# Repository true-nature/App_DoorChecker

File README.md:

App_DoorChecker
===============

The wireless monitor of the door lock up status.
It works on ToCoS TWE-Lite.

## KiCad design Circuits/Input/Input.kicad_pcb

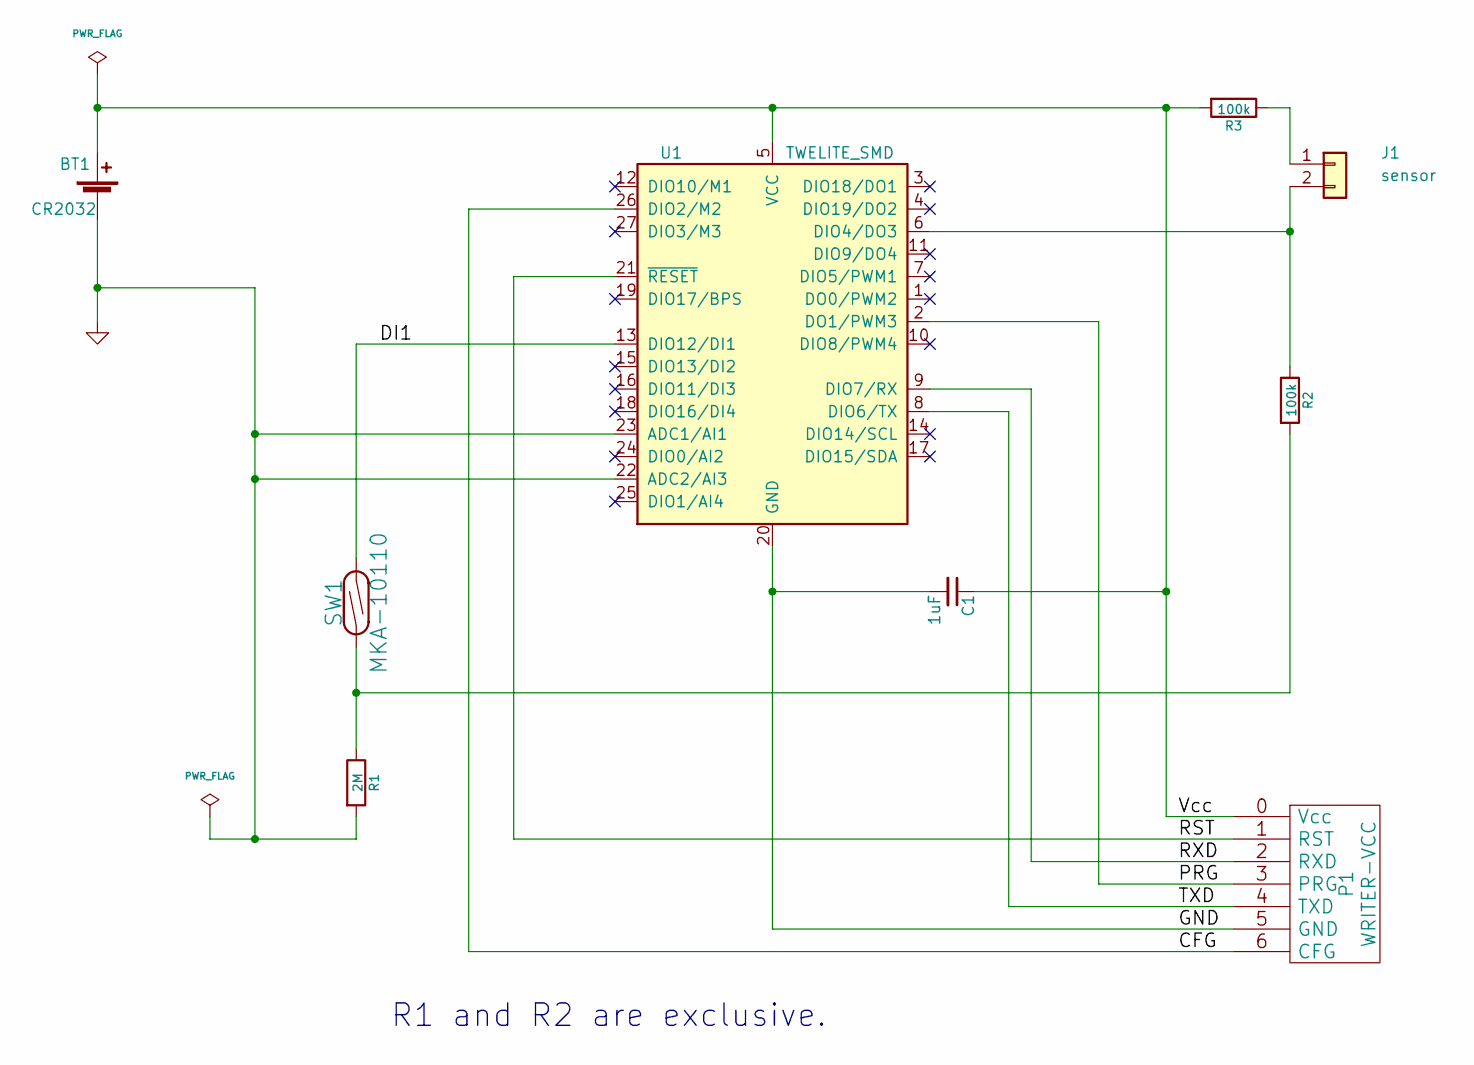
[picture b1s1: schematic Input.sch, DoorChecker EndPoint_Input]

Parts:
BT1: CR2032; PBCS-75
C1: 1uF; C_0603_1608Metric_Pad0.84x1.00mm_HandSolder
J1: sensor; PinHeader_2x01_P2.54mm_Vertical
P1: WRITER-VCC; WRITE-7P
R1: 2M; R_0603_1608Metric_Pad0.84x1.00mm_HandSolder
R2, R3: 100k; R_0603_1608Metric_Pad0.84x1.00mm_HandSolder
SW1: MKA-10110
U1: TWELITE_SMD

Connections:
/CFG: P1.6 (CFG), U1.26 (DIO2/M2)
/DI1: SW1.2, U1.13 (DIO12/DI1)
/PRG: P1.3 (PRG), U1.2 (DO1/PWM3)
/RST: P1.1 (RST), U1.21 (~RESET)
/RXD: P1.2 (RXD), U1.9 (DIO7/RX)
/TXD: P1.4 (TXD), U1.8 (DIO6/TX)
/Vcc: BT1.1 (+), C1.1, P1.0 (Vcc), R3.2, U1.5 (VCC)
GND: BT1.2 (-), C1.2, P1.5 (GND), R1.2, U1.20 (GND), U1.22 (ADC2/AI3), U1.23 (ADC1/AI1), U1.28 (GND), U1.30 (GND), U1.31 (GND), U1.32 (GND)
unnamed: J1.1, R3.1
unnamed: J1.2, R2.1, U1.6 (DIO4/DO3)
unnamed: R1.1, R2.2, SW1.1

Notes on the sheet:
R1 and R2 are exclusive.

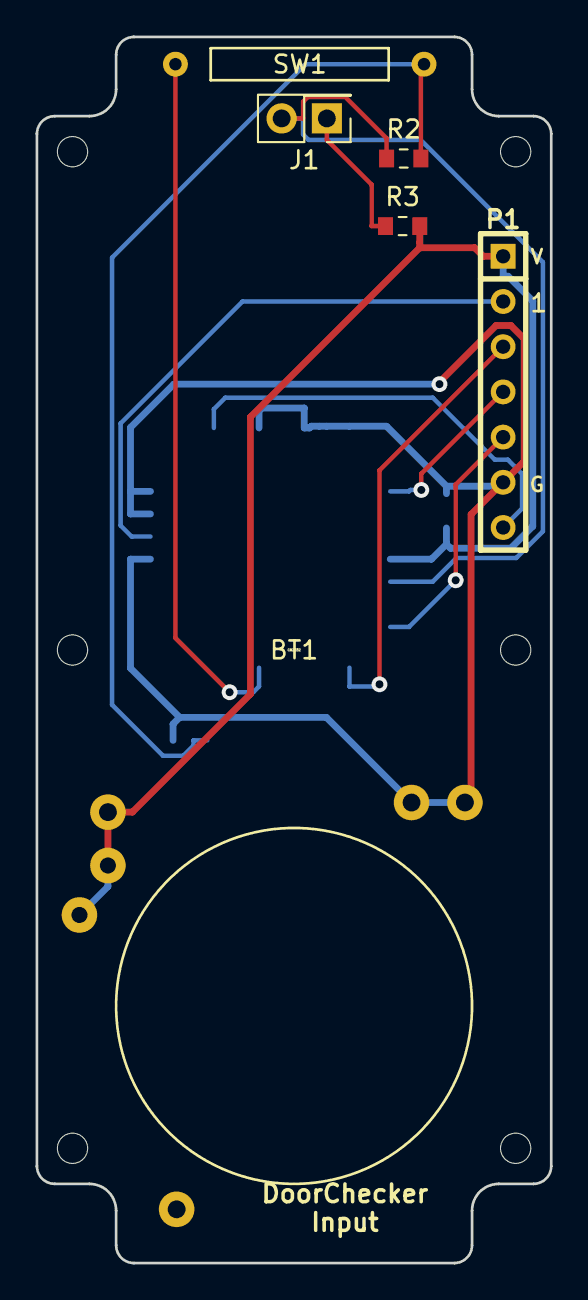
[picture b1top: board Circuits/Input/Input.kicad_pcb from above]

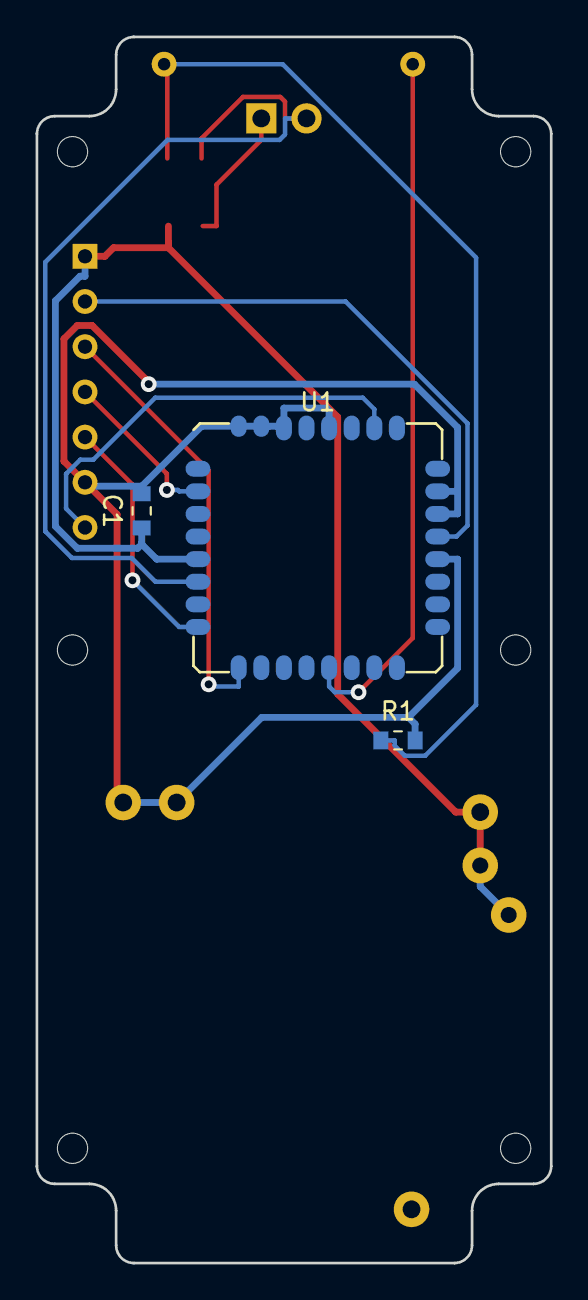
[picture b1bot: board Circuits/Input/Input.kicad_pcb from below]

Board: 2 copper layers, 28.9 x 68.9 mm, 9 parts (3 on the bottom side), 11 nets.

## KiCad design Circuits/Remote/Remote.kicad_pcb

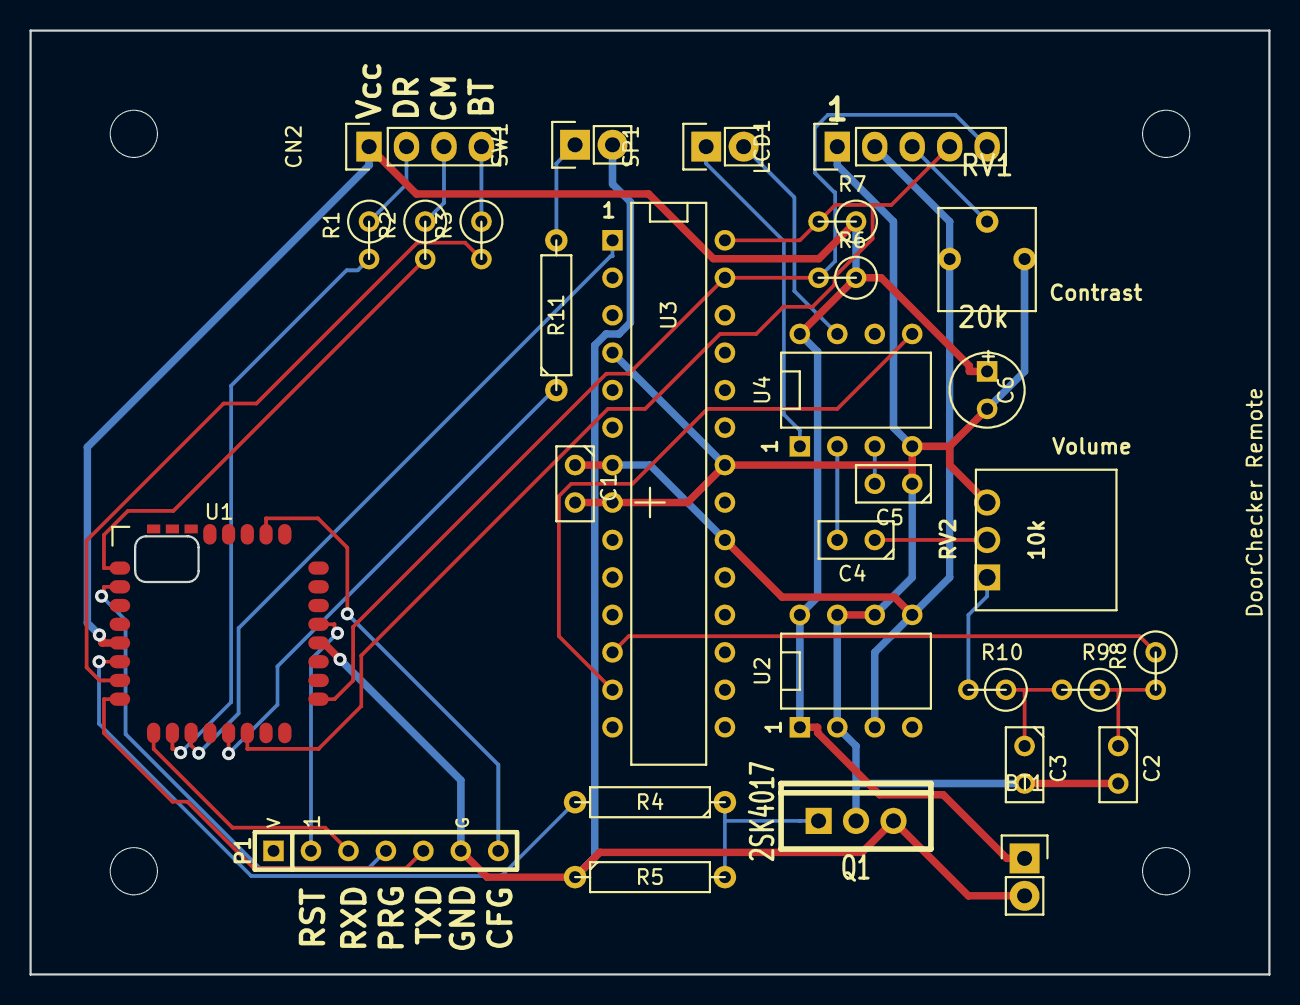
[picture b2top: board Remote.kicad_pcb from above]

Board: 2 copper layers, 84.0 x 64.0 mm, 31 parts (0 on the bottom side), 33 nets.

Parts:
BT1: BATTERY; Pin_Header_Straight_1x02
C1: 0.1u; C1
C2: 0.047u; C1
C3: 0.01u; C1
C4, C5: 1u; C1
C6: 47u; C1V5
CN2: CONN_4; Pin_Header_Straight_1x04
DoorChecker Remote: VAL**; PB-SGM-135
LCD1: AQM1602NI; Pin_Header_Straight_1x05
P1: WRITER-VCC; WRITE-7P
Q1: 2SK4017; TO220_VERT_GDS
R1, R2, R3: 680; R1
R4: 1k; R4
R5: 2.2M; R4
R6, R7, R10: 10k; R1
R8: 1k; R1
R9: 4.7k; R1
R11: 10k; R4
RV1: 20k; RV-3362P
RV2: 10k; RV-TSR-3386T
SP1: SPEAKER; Pin_Header_Straight_1x02
SW1: WakeUp; Pin_Header_Straight_1x02
U1: TWE_LITE_SMD; TWE-001L-SMD
U2: STEPUP3.3V; DIP-8__300
U3: ATP3011-PU; DIP-28__300
U4: HT82V739; DIP-8__300

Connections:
/3.3VOUT: C1.1, LCD1.2, RV1.1, U2.3, U2.5, U3.7, U3.20
/AOUT: R8.1, U3.12
/AudioIn: C4.2, U4.2
/BATT: CN2.4, R3.1
/COMM: CN2.3, R2.1
/DOOR: CN2.2, R1.1
/GND_SW: R4.2, U1.6
/Gate: Q1.G, R4.1, R5.2
/LPF1: C2.1, R8.2, R9.1
/LPF2: C3.1, R9.2, R10.1
/LPF3: R10.2, RV2.1
/M2: P1.6, U1.26
/PLAY#: U3.13, U4.5
/PRG: P1.3, U1.2
/PWM1: R3.2, U1.7
/PWM2: R2.2, U1.1
/PWM4: R1.2, U1.10
/QGND: C1.2, C2.2, C3.2, C5.1, C6.2, LCD1.1, Q1.D, RV1.3, RV2.3, U2.2, U2.6, U2.7, U3.4, U3.8, U3.22, U4.4
/RESET#: U1.11, U3.1
/RST: P1.1, U1.21
/RXD: P1.2, U1.9
/SCL: LCD1.4, R7.2, U1.14, U3.28
/SDA: LCD1.5, R6.2, U1.17, U3.27
/SPK+: SP1.1, U4.1
/SPK-: SP1.2, U4.7
/SW: R11.2, SW1.1
/TXD: P1.4, U1.8
/V0: LCD1.3, RV1.2
/VOL: C4.1, RV2.2
/VREF: C5.2, U4.3
/WUP: R11.1, U1.13
GND: BT1.2, P1.5, Q1.S, R5.1, SW1.2, U1.20
VCC: BT1.1, C6.1, CN2.1, R6.1, R7.1, U1.5, U2.1, U2.8, U4.8

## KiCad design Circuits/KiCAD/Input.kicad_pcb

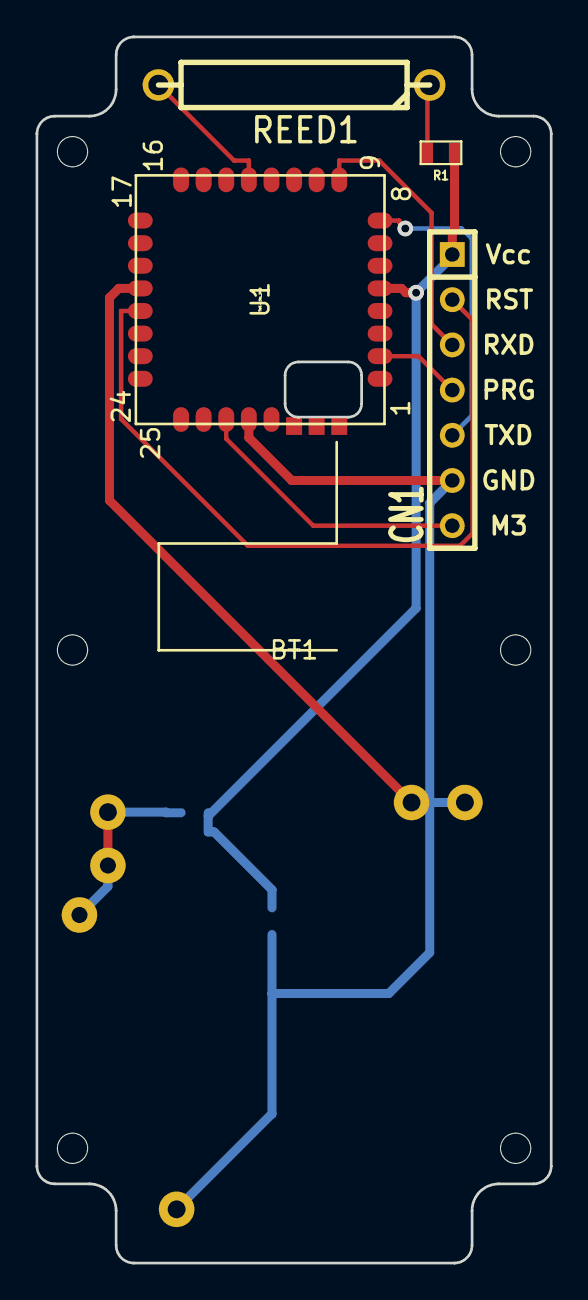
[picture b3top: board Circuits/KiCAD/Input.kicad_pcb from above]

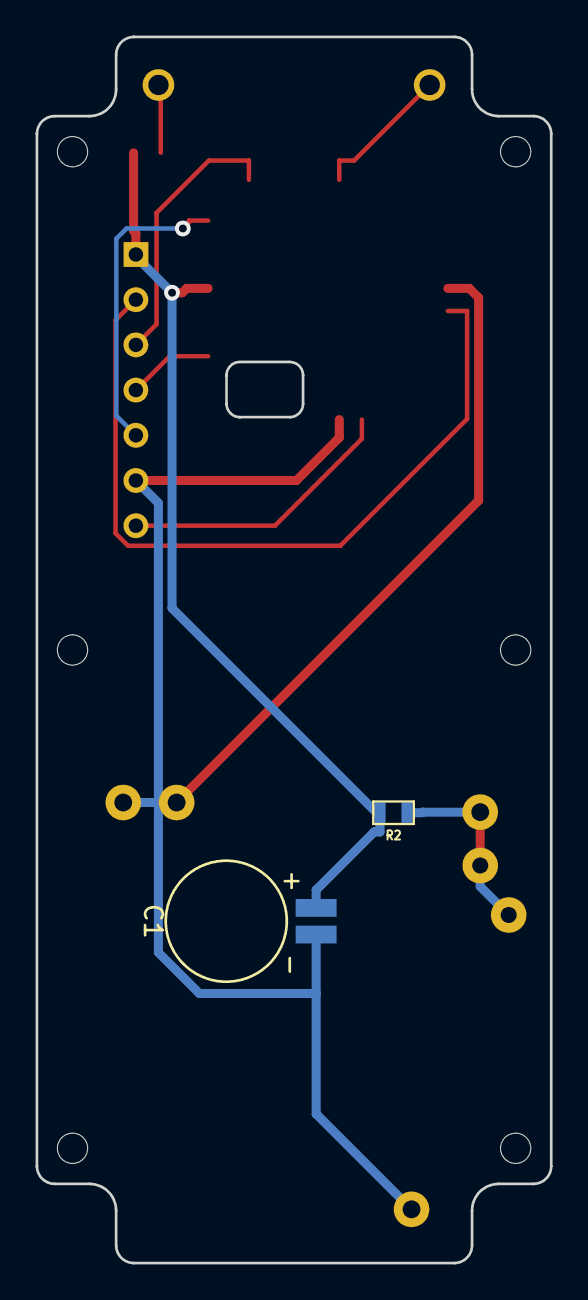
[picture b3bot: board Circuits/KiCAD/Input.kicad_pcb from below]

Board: 2 copper layers, 28.9 x 68.9 mm, 7 parts (2 on the bottom side), 10 nets.

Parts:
BT1: CR2032; PBCS-75
C1: 0.22; DCK-3R3E224-E
CN1: WRITER; SIL-7
R1: 2M; SM0603
R2: 75; SM0603
REED1: SPST; R6
U1: TWE-Lite_SMD; TWE-001L-SMD

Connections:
/CFG: CN1.7, U1.27
/DC3V: BT1.1, R2.1
/DOOR: REED1.2, U1.13
/PRG: CN1.4, U1.2
/PULLUP: R1.1, REED1.1
/RST: CN1.2, U1.21
/RX: CN1.3, U1.9
/TX: CN1.5, U1.8
GND: BT1.2, C1.2, CN1.6, U1.20, U1.28
VCC: C1.1, CN1.1, R1.2, R2.2, U1.5

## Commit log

2014-09-25 Ignore firmware binaries.
2014-09-25 Updated project description.
2014-09-25 Imported from Samp_Monitor v1.3.2 project.
2014-09-25 Updated to Samp_Monitor v1.3.3.
2014-09-25 Changed application name.
2014-09-25 Eclipseのコード解釈エラーを解決。
2014-09-25 プルアップ停止判定のタイミングを確認するToDoタスクを追加。
2014-09-25 Making up a ToDo list.
2014-09-26 ToDo項目をリストアップ中。
2014-09-26 readmeの中身を改造後の予定動作に差し替え。
2014-09-26 EEPROM読み込み前では設定値がプルアップ判定に反映されないので、読み込み後に移動。
2014-09-27 Eclipseのコード解釈エラーを解消。
2014-09-27 子機のドアアラームを無効化。定期的に状態送信を有効化。
2014-09-27 App_Twelite v1.7の実験的な実装からI2C接続LCDのコードをコピー。
2014-09-27 I2C LCD functions are ready to call.
2014-09-27 子機の数をEEPROMに記憶。
2014-09-27 実装が済んだToDoのマークアップを削除。
2014-09-28 子機使用状況を最大数でなく使用IDのマスクで管理する。
2014-09-28 ADCを有効にして電源電圧をモニターする。
2014-09-28 32bit all 1は特異値なので使用不可。ビット数を減らして子機は最大30とする。
2014-09-28 flash.cがconfig.hをincludeしないので無条件でフィールド追加。
2014-09-28 u32idmaskは0にできない。
2014-09-28 パケット受信時にスイッチ状態、子機ID,電源電圧を保存。
2014-09-28 配列の先頭から使用する。
2014-09-28 2行8桁のLCDで表示できる数に制限。
2014-09-28 I2C LCD(AQM0802A)でステータスを表示する。
2014-09-28 通信途絶の場合は低電圧と同じ表示。
2014-09-29 Designing the circuit.
2014-09-29 Revert "子機のドアアラームを無効化。定期的に状態送信を有効化。"
    This reverts commit 1dabc5c033cbefd2f427b25f9b8f2b4ddbc21269.
    Conflicts:
    Common/Source_User/config.h
    EndDevice_Input/Source/ProcessEv_Door_Timer.c
2014-09-29 子機モード51からFEへ軌道変更。
2014-09-29 PKT_ID_BOTTON用に変更中。
2014-09-29 tsRxPktInfoをアドレス私に変更。
2014-09-29 子機モード0x51(PKT_ID_BOTTON)を定時送信化して戸締りチェッカー再実装。
2014-09-29 Moved I2C_impl to Common. Endpoint_Remote will use it.
2014-09-30 機能別に回路図をInput,Parent,Remoteの3部構成とする。
2014-09-30 確認UIをParentからRemoteへ移動。
2014-09-30 ToDoをParentからRempoteへ引っ越し。
2014-09-30 AQM0802Aへの状態表示をParentからRemoteへ移植。
2014-09-30 Moved circuit design data.
2014-09-30 AppIdを親機候補のSerial No.ベースに変更。 戸締り情報をMessagePoolに乗せてRemoteで表示できるようになった。
2014-09-30 Remote起動時にLCD初期化。
2014-09-30 16台目の子機が表示されないバグを修正。
2014-09-30 備忘録をToDoに追加。
2014-09-30 LCD(AQM0802A)のGNDをFETでスイッチする。
2014-10-01 ParentからI2C LCD表示を削除。
2014-10-01 RemoteのPWM1,2,4で電源、窓開け、通信のエラー状態を表示。
2014-10-01 電池駆動でも読めるコントラストに調整。
2014-10-01 LEDをsink制御に変更。
2014-10-01 LED表示を数秒間継続。スリープ時に消灯。
2014-10-01 子機再登録モードのToDoを追加。
2014-10-01 LCDをACM1602に変更。
2014-10-01 基板レイアウトをPaasで作成してみる。
2014-10-01 親機にLEDと圧電スピーカーを追加。
2014-10-02 実体配線図を作成。
2014-10-02 SLEEP#のプルアップを停止。
2014-10-03 予定動作の説明を、ボタン起動モード、リモート子機を含む三部構成に変更。
2014-10-03 DO3でLCTとATPの電源を制御。DI2で音声再生の終了待ち確認。
2014-10-03 Q1の保護ダイオードを追加。Q2は寄生ダイオードが内蔵されているので不要。
2014-10-03 音声合成の枠組みだけ作成。
2014-10-04 SMOD0接地、PLAYをDI3で検出。
2014-10-04 ATP3012を使用した音声案内を実装。
2014-10-04 memccpy()の用法ミスを修正。
2014-10-04 基板名を付加
2014-10-04 デバッグ用のprintを削除。
2014-10-05 イントネーション修正、デバッグprint削除。
2014-10-06 3.3V電源はDC StepUpコンバータで昇圧供給。
2014-10-06 メッセージ数可変方式に変更。 PLAY検出ではbusyの代用にならないので、ポーリングでATPのbusyを確認する。
2014-10-06 ATP301xへのリセットを追加。PLAY/への結線を廃止。
2014-10-06 DC昇圧モジュール名にHT7733A moduleを採用。
2014-10-06 AKI B基板で作る予定は無くなった。
2014-10-06 HT7733A 昇圧型ＤＣＤＣコンバータ ＳｔｅｐＵＰ・ＤＩＰをライブラリに追加。
2014-10-07 EDLCの単位間違いを修正。
2014-10-07 圧電スピーカーにダイオードを接続。
2014-10-07 Speakerの＋側をHT7733Aから供給。
2014-10-07 問題なく動作する部分のToDoコメントを削除。
2014-10-07 表示中の再生中断とMessagePool再要求を可能にする。
2014-10-07 Endpoint_InputからADCコードを移植中。
2014-10-07 Abortは応答を待たない。
2014-10-07 ADC初期化失敗するので保留。 ACM1602も接続。
2014-10-07 不要になった受信バッファを削除。
2014-10-07 WarmStartでADCが初期化されないバグを修正。
2014-10-07 Remote子機の電圧チェックが動作。表示は未完。
2014-10-07 窓以外の通信エラーと電池警告の表示をToDoにメモ。
2014-10-08 表示中の再問い合わせ、Remote子機電池残量チェックを実装したのでToDo削除。
2014-10-09 Removed unused variable.
2014-10-09 ACM1602の2行目にメッセージ文字列を表示。 親機通信エラーは1行目にもメッセージ表示。
2014-10-09 Designing PCB.
2014-10-10 カタカナがUTF-8でエンコードされていたバグを修正。
2014-10-11 ADCを待ってから表示開始。再スタート時にADCも再計測。
2014-10-11 DCコンバータを実体配線図に追加。
2014-10-12 正常時にRemote子機自身の電圧を表示。 電源は液晶のバックライトで確認できるため、正常時はLED点灯無し。 LED配置換え。
2014-10-12 M2の結線位置を訂正。
2014-10-12 電池残量警告のｲﾝﾃﾞｯｸｽ名を修正。
2014-10-13 KiCAD,EAGLEでのPCB設計を試行中。
2014-10-13 LCDでも3.3V電源を使用するため、音声合成はATP3011でなくATP3012で確定。
2014-10-13 TWE-Lite SMDのフットプリントをデータシートから作成中。
2014-10-14 TWE-Lite SMDのパッド位置修正、外形線追加。
2014-10-14 TWE-EH版のセンサー子機回路図を追加。
2014-10-15 タカチCST-2032をライブラリに追加(名前だけ)。
2014-10-16 CST-2032のスルーホール位置を決定。
2014-10-16 結線用スルーホール追加。
2014-10-20 コピー結果が化けるので、S_OCTET(G_OCTET())の羅列をmemcpy()に置き換えた。
2014-10-21 Fixed typo.
2014-10-21 出力がUartモードの場合もpRxPktInfoのメンバに受信した値をセットする。
2014-10-21 TWE-EH Solar版回路図を差し替え。
2014-10-21 M2をGNDと隣接するCFG#コネクタへ接続。
2014-10-23 Increased expiration timeout from 1 to 3 minutes.
2014-10-25 Router動作中にPWM4に接続したLEDを点滅させる。
2014-11-02 ボタン状態に応じて割り込みエッジを選択する。
2014-11-02 Eagleデータは不要。
2014-11-03 HT82V739,ATP3011を使う回路図を作成。
2014-11-04 Fixed pin no of DC Step Up Converter.
2014-11-04 Fixed pin no of HT82V739.
2014-11-04 ATP3011版の実体配線図を追加。
2014-11-04 アナログセンサ用の転記処理を修正。
2014-11-05 ATP3011版の実体配線図完成。
2014-11-05 回路図画像を追加。
2014-11-06 ATP3011のGNDを配線。LCD電源の配線統合を反映。
2014-11-11 書き換え用ピンヘッダを7ピンに修正。
2014-11-16 Added scripts for Raspberry Pi.
2014-11-16 Added MRTG configuration.
2014-11-25 Read mail addresses from config file.
2014-12-09 ERC checked.
2014-12-09 Vcc,GNDラインにラベル追加。
2014-12-24 Updated KiCAD data.
2014-12-25 ERC passed.
2015-01-18 Copied libraries from BicycleFinder.
2015-01-19 Assigned PBCS-75 as battery holder.
2015-01-19 Added small EDLC module.
2015-01-20 Use chip registers.
2015-01-20 Creating 3D model of CS-75 plastic case.
2015-01-21 Moved BSch3V data to subdirectory.
2015-01-21 Renamed directory.
2015-01-21 Moved libraries to ../kicad-twe.
2015-01-21 Added 3D model of pinheader.
2015-01-21 Created KiCAD project for DoorChecker Remote.
2015-01-21 Fixed: Reed switch was not connected to GND.
2015-01-22 Added DC-DC converter module.
2015-01-23 Copied schematic diagram from BSch3V to KiCAD.
2015-01-23 Assigned footprint.
2015-01-23 Consider NTH.
2015-01-25 Modified parts layout.
2015-01-25 Replaced RV2 to RV-3362P.
2015-01-25 Renamed RV-TSR-3386T.
2015-01-26 Changed PCB thickness.
2015-01-27 Updated 3D model.
2015-01-27 Moved ATP.
2015-01-27 Re-layout by FreeRouting.
2015-01-28 Moved LED out of the PCB via pin header.
2015-01-29 Set inhibit area under CR2032.
2015-01-29 Replaced footprint of TWE-Lite SMD with antenna hole.
2015-01-29 Supply 2/3 divided volt to adc2.
2015-01-30 Moved silk position.
2015-01-31 Ordered to PCB prototyping service.
2015-02-01 Removed BOM list.
2015-02-06 Moved location of 3D models.
2015-02-23 Replaced a EDLC to an array of MLCC.
2015-02-26 Added 3D model of ACM1602NI LCD.
2015-03-01 Store WakeUpByButton field after flash load.
2015-03-02 Added a voltage monitor.
2015-03-07 Show door status in rain notification.
2015-03-08 Fixed: Switch to configuration mode by M2.
2015-03-08 Changed register value from 75 to 1k.
2015-03-15 Merged raw dump into parsed output file.
2015-03-16 Use both M2 and M3 for configuration switch.
2015-03-16 Start to edit current KiCad.
2015-03-22 Modified reset circuit.
2015-03-23 Migrating to current version of KiCad.
2015-03-28 Changed library file name from TWE-Lite to favorites.
2015-04-26 Limit rain alert frequency less than one per an hour.
2015-05-09 Fixed: Dump file was not saved.
2015-10-19 Simplified power supply block.
2015-10-26 Turn off the LED connected to DO1.
2015-11-29 Added email filter program to fetch door status.
2015-11-29 Updated library list.
2016-04-18 Changed location of 3d shapes.
2016-05-02 Added the monitor script for TWE-Lite 2525A.
2016-05-09 Replaced the FET symbol.
2017-01-22 Catch exception thrown by binascii.unhexlify().
2017-01-25 Identify rain sensor by Logical Id.
2017-06-17 Fixed format string.
2017-06-17 Fixed octal number.
2017-06-17 Read serial data as bytes.
2017-06-17 Migrated to Python3.
2018-01-03 雨センサー基板を作成
2018-02-14 Updated libraries
2018-02-14 Replaced SMD by DIP
2018-02-15 Replaced sensor to pinheader
2018-03-07 Migrating to KiCad 5.0
2018-03-09 Removed rescue library
2018-03-14 Updated footprint
2018-03-19 Updated symbols
2018-03-21 ADC2をGNDに配線
2018-03-26 Updated symbol of TWELITE
2019-03-23 Break when an exception has caught
2019-03-30 Updated by working script
